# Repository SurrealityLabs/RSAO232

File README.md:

# RSAO232
Because badges need RS232 Serial ports

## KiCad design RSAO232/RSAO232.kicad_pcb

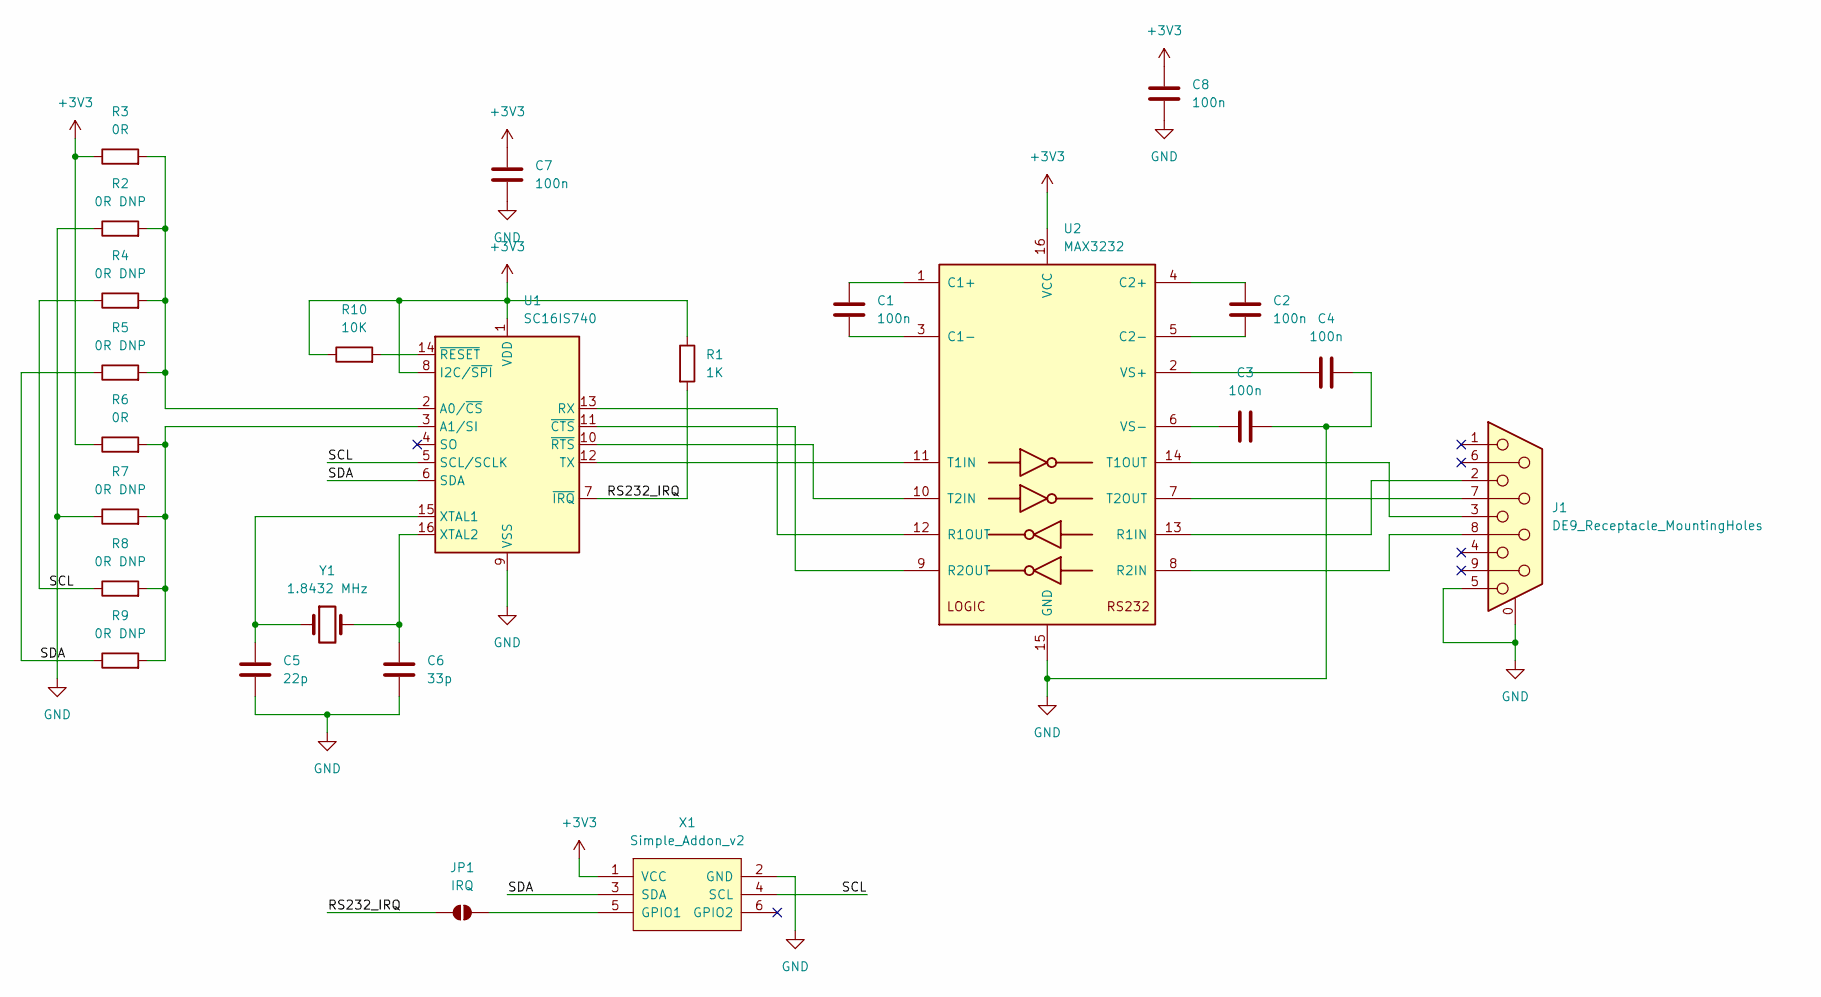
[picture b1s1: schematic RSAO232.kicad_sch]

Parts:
C1, C2, C3, C4, C7, C8: 100n; C_0603_1608Metric_Pad1.08x0.95mm_HandSolder
C5: 22p; C_0603_1608Metric_Pad1.08x0.95mm_HandSolder
C6: 33p; C_0603_1608Metric_Pad1.08x0.95mm_HandSolder
J1: DE9_Receptacle_MountingHoles; DSUB-9_Female_Vertical_P2.77x2.84mm_MountingHoles
JP1: IRQ; SolderJumper-2_P1.3mm_Open_RoundedPad1.0x1.5mm
R1: 1K; R_0603_1608Metric_Pad0.98x0.95mm_HandSolder
R2, R4, R5, R7, R8, R9: 0R DNP; R_0603_1608Metric_Pad0.98x0.95mm_HandSolder
R3, R6: 0R; R_0603_1608Metric_Pad0.98x0.95mm_HandSolder
R10: 10K; R_0603_1608Metric_Pad0.98x0.95mm_HandSolder
U1: SC16IS740; TSSOP-16_4.4x5mm_P0.65mm
U2: MAX3232; SOIC-16_3.9x9.9mm_P1.27mm
X1: Simple_Addon_v2; Simple_Addon_v2-SAO-2x3-SMD
Y1: 1.8432 MHz; Crystal_SMD_HC49-SD

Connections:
+3V3: C7.1, C8.1, R1.1, R3.1, R6.1, R10.1, U1.1 (VDD), U1.8 (I2C/~SPI), U2.16 (VCC), X1.1 (VCC)
/RS232_IRQ: JP1.1 (A), R1.2, U1.7 (~IRQ)
/SCL: R4.1, R8.1, U1.5 (SCL/SCLK), X1.4 (SCL)
/SDA: R5.1, R9.1, U1.6 (SDA), X1.3 (SDA)
GND: C3.2, C4.2, C5.2, C6.2, C7.2, C8.2, J1.0 (PAD), J1.5, R2.1, R7.1, U1.9 (VSS), U2.15 (GND), X1.2 (GND)
unnamed: JP1.2 (B), X1.5 (GPIO1)
unnamed: R2.2, R3.2, R4.2, R5.2, U1.2 (A0/~CS)
unnamed: R6.2, R7.2, R8.2, R9.2, U1.3 (A1/SI)
unnamed: U1.13 (RX), U2.12 (R1OUT)
unnamed: U1.12 (TX), U2.11 (T1IN)
unnamed: C5.1, U1.15 (XTAL1), Y1.1
unnamed: C6.1, U1.16 (XTAL2), Y1.2
unnamed: U1.11 (~CTS), U2.9 (R2OUT)
unnamed: R10.2, U1.14 (~RESET)
unnamed: U1.10 (~RTS), U2.10 (T2IN)
unnamed: C1.1, U2.1 (C1+)
unnamed: C1.2, U2.3 (C1-)
unnamed: C2.1, U2.4 (C2+)
unnamed: C2.2, U2.5 (C2-)
unnamed: J1.2, U2.13 (R1IN)
unnamed: J1.8, U2.8 (R2IN)
unnamed: J1.3, U2.14 (T1OUT)
unnamed: J1.7, U2.7 (T2OUT)
unnamed: C4.1, U2.2 (VS+)
unnamed: C3.1, U2.6 (VS-)

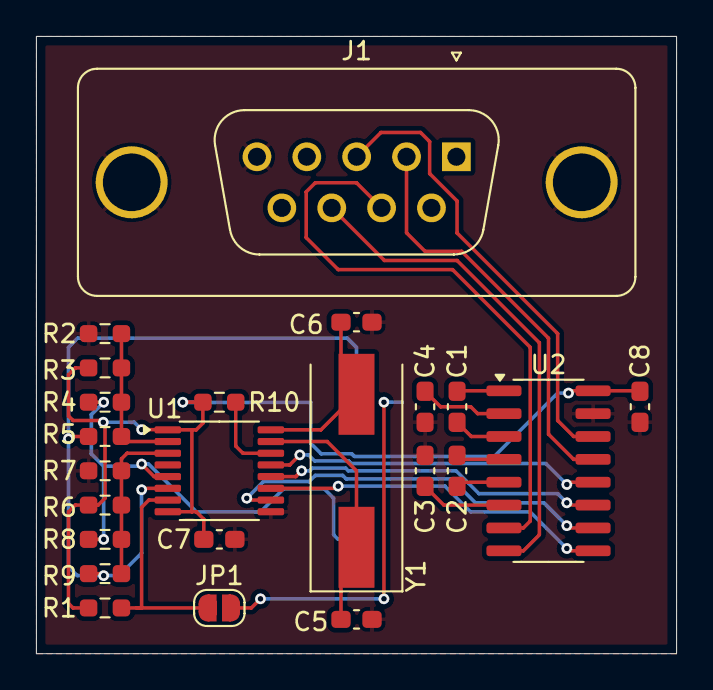
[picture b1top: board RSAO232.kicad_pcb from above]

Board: 2 copper layers, 35.6 x 34.3 mm, 24 parts (1 on the bottom side), 25 nets.

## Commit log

2024-11-20 Started work on schematic
2024-11-27 Almost finished schematic and layout, probably need a bit more bulk capacitance
